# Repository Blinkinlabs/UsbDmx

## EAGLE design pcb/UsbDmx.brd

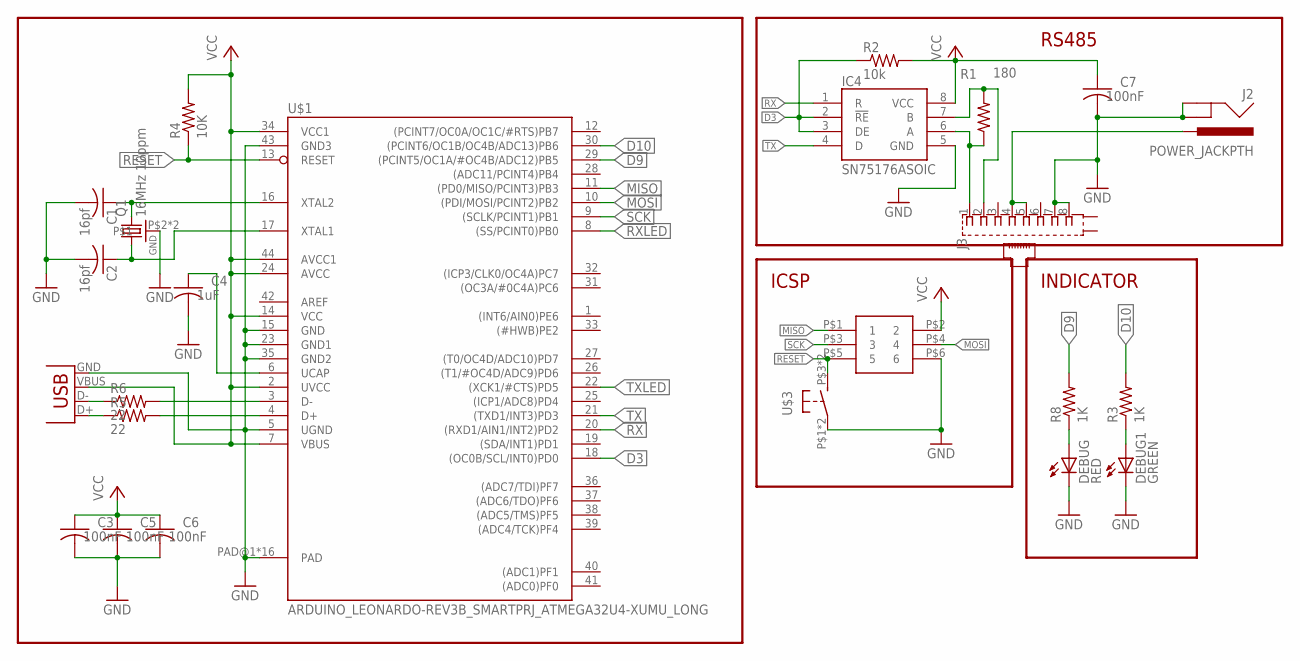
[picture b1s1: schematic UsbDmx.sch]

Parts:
C1, C2: 16pf; C0603
C3, C5, C6, C7: 100nF; C0603
C4: 1uF; C0603
DEBUG: RED; LED-0805
DEBUG1: GREEN; LED-0805
IC4: SN75176ASOIC; SO08
J2: POWER_JACKPTH; POWER_JACK_PTH
J3: 555153-1
Q1: 16MHz 10ppm; CRSYTAL_2520
R1: 180; R0603
R2: 10k; R0603
R3, R8: 1K; R0603
R4: 10K; R0603
R5, R6: 22; R0603
U$1: ARDUINO_LEONARDO-REV3B_SMARTPRJ_ATMEGA32U4-XUMU_L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; QFN44ML7X7_LONGLEADS
U$2: 2X3HEADER
U$3: BUTTON_MOMENTARY; BUTTON_MOMENTARY_KMR211G
X1: USBPTH; USB-B-PTH

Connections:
AREF: U$1.42 (AREF)
D3: IC4.2 (!RE), IC4.3 (DE), R2.1, U$1.18 ((OC0B/SCL/INT0)PD0)
D9: R8.2, U$1.29 ((PCINT5/OC1A/#OC4B/ADC12)PB5)
D10: R3.2, U$1.30 ((PCINT6/OC1B/OC4B/ADC13)PB6)
GND: C1.2, C2.2, C3.2, C4.2, C5.2, C6.2, C7.2, DEBUG.C, DEBUG1.C, IC4.5 (GND), J2.GND, J2.GNDBREAK, J3.7, J3.8, Q1.P$2, Q1.P$4, U$1.5 (UGND), U$1.15 (GND), U$1.23 (GND1), U$1.35 (GND2), U$1.43 (GND3), U$1.PAD@1 (PAD), U$1.PAD@2 (PAD), U$1.PAD@3 (PAD), U$1.PAD@4 (PAD), U$1.PAD@5 (PAD), U$1.PAD@6 (PAD), U$1.PAD@7 (PAD), U$1.PAD@8 (PAD), U$1.PAD@9 (PAD), U$1.PAD@10 (PAD), U$1.PAD@11 (PAD), U$1.PAD@12 (PAD), U$1.PAD@13 (PAD), U$1.PAD@14 (PAD), U$1.PAD@15 (PAD), U$1.PAD@16 (PAD), U$2.P$6 (6), U$3.P$1, U$3.P$2, X1.GND
MISO: U$1.11 ((PD0/MISO/PCINT3)PB3), U$2.P$1 (1)
MOSI: U$1.10 ((PDI/MOSI/PCINT2)PB2), U$2.P$4 (4)
unnamed: R6.1, X1.D-
unnamed: C1.1, Q1.P$3 (2), U$1.16 (XTAL2)
unnamed: R5.1, X1.D+
unnamed: R5.2, U$1.4 (D+)
unnamed: C2.1, Q1.P$1 (1), U$1.17 (XTAL1)
unnamed: R6.2, U$1.3 (D-)
unnamed: DEBUG1.A, R3.1
unnamed: DEBUG.A, R8.1
unnamed: C4.1, U$1.6 (UCAP)
RESET: R4.1, U$1.13 (RESET), U$2.P$5 (5), U$3.P$3 (S), U$3.P$4 (S)
RS485A: IC4.6 (A), J3.1, R1.1
RS485B: IC4.7 (B), J3.2, R1.2
RX: IC4.1 (R), U$1.20 ((RXD1/AIN1/INT2)PD2)
RXLED: U$1.8 ((SS/PCINT0)PB0)
SCK: U$1.9 ((SCLK/PCINT1)PB1), U$2.P$3 (3)
TX: IC4.4 (D), U$1.21 ((TXD1/INT3)PD3)
TXLED: U$1.22 ((XCK1/#CTS)PD5)
VCC: C3.1, C5.1, C6.1, C7.1, IC4.8 (VCC), R2.2, R4.2, U$1.2 (UVCC), U$1.7 (VBUS), U$1.14 (VCC), U$1.24 (AVCC), U$1.34 (VCC1), U$1.44 (AVCC1), U$2.P$2 (2), X1.VBUS
VMOT: J2.PWR, J3.4, J3.5

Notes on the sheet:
RS485
ICSP
INDICATOR

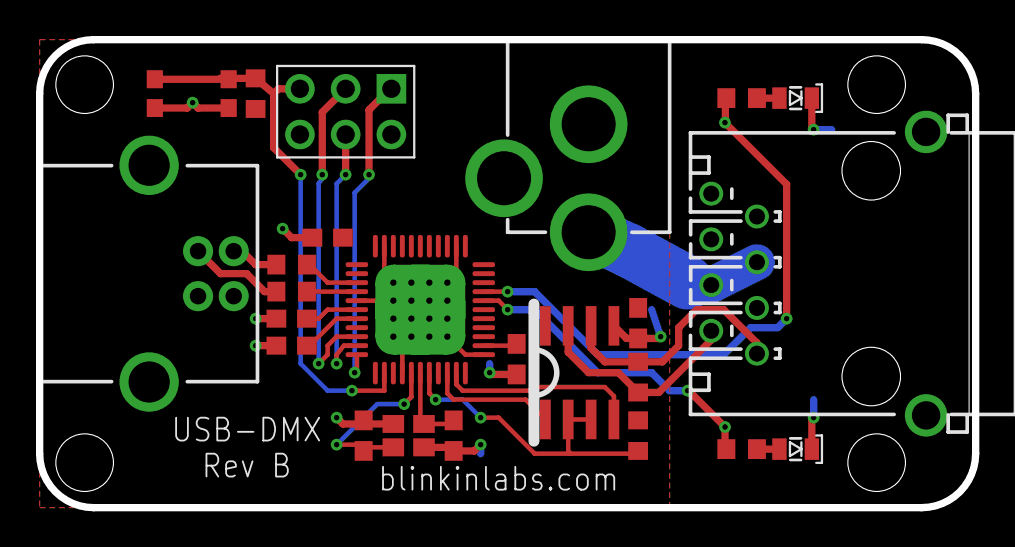
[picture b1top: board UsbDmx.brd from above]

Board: 2 copper layers, 52.0 x 26.0 mm, 24 parts (0 on the bottom side), 23 nets.

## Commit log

2012-12-31 First board commit
2012-12-31 Replaced crystal with smaller 3025 version, placed and routed all passives.
    TODO: finish routing processor ground, final check, assemble BOM.
2013-01-02 Fixed processor thermal vias (no more DRC errors), finished ground routing, added missing UCAP
2013-01-02 Hopefully RevA.
2013-03-08 Simple firmware
2013-03-29 Tweak speed, add TODOs. Still not ready for prime time- data rate is too low.
2013-05-09 Add first pass at a non-arduino firmware, for speed.
2013-06-09 Fix bugs so that the LUFA-based firmware works with 250K serial.
2013-06-10 Update usb_serial for new gcc
2013-10-07 Update library name
2014-03-08 RevB, as submitted
